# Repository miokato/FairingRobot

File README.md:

#1 This is Robot Car repository.

# I modified some repository.
This is master branch.

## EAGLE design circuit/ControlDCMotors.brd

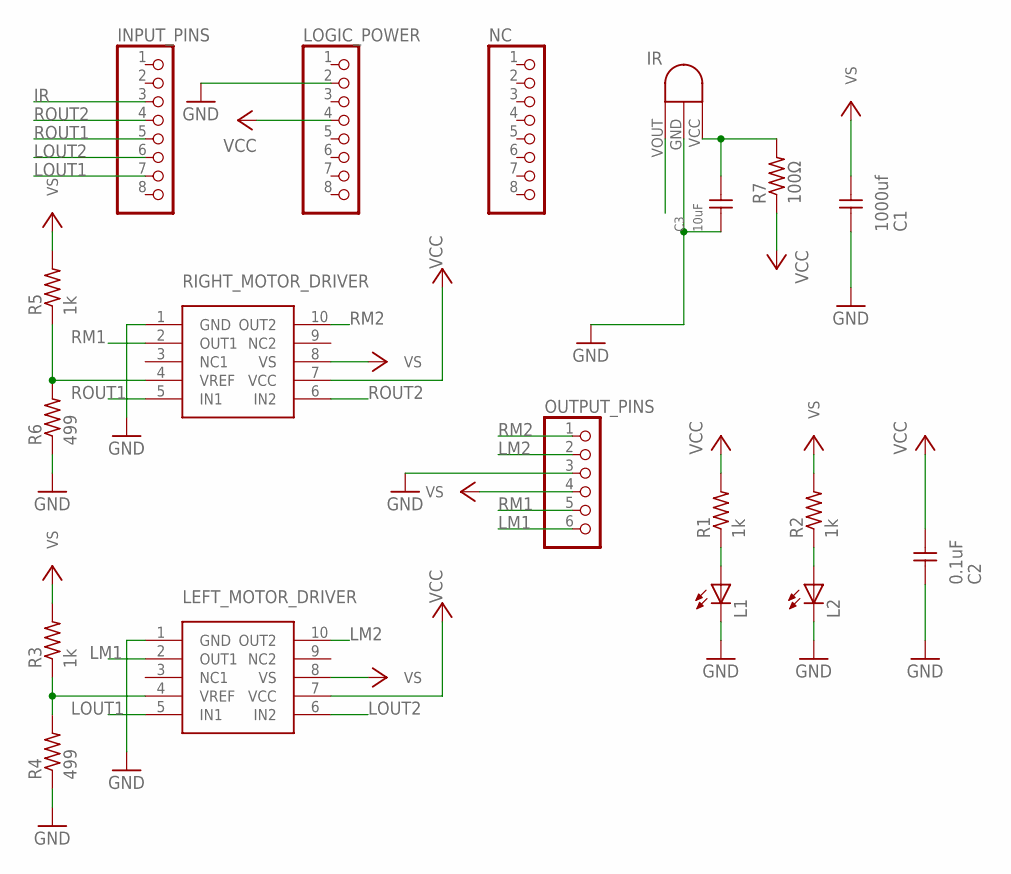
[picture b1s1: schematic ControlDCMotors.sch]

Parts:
C1: 1000uf; EPOL5_10.5
C2: 0.1uF; 1206
C3: 10uF; 1206
INPUT_PINS: PINHD-1X8; 1X08
IR_SENSOR: IR_SENSOR
L1, L2: LED1608
LEFT_MOTOR_DRIVER: TA7291P; HSIP10_P_2.54
LOGIC_POWER: PINHD-1X8; 1X08
NC: PINHD-1X8; 1X08
OUTPUT_PINS: PINHD-1X6; 1X06
R1, R2, R3, R5: 1k; 1206
R4, R6: 499; 1206
R7: 100Ω; 1206
RIGHT_MOTOR_DRIVER: TA7291P; HSIP10_P_2.54

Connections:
GND: C1.-, C2.1, C3.1, IR_SENSOR.GND, L1.C, L2.C, LEFT_MOTOR_DRIVER.1 (GND), LOGIC_POWER.2, OUTPUT_PINS.3, R4.1, R6.1, RIGHT_MOTOR_DRIVER.1 (GND)
IR: INPUT_PINS.3, IR_SENSOR.VOUT
LM1: LEFT_MOTOR_DRIVER.2 (OUT1), OUTPUT_PINS.6
LM2: LEFT_MOTOR_DRIVER.10 (OUT2), OUTPUT_PINS.2
LOUT1: INPUT_PINS.7, LEFT_MOTOR_DRIVER.5 (IN1)
LOUT2: INPUT_PINS.6, LEFT_MOTOR_DRIVER.6 (IN2)
unnamed: L1.A, R1.1
unnamed: L2.A, R2.1
unnamed: R5.1, R6.2, RIGHT_MOTOR_DRIVER.4 (VREF)
unnamed: LEFT_MOTOR_DRIVER.4 (VREF), R3.1, R4.2
unnamed: C3.2, IR_SENSOR.VCC, R7.2
RM1: OUTPUT_PINS.5, RIGHT_MOTOR_DRIVER.2 (OUT1)
RM2: OUTPUT_PINS.1, RIGHT_MOTOR_DRIVER.10 (OUT2)
ROUT1: INPUT_PINS.5, RIGHT_MOTOR_DRIVER.5 (IN1)
ROUT2: INPUT_PINS.4, RIGHT_MOTOR_DRIVER.6 (IN2)
VCC: C2.2, LEFT_MOTOR_DRIVER.7 (VCC), LOGIC_POWER.4, R1.2, R7.1, RIGHT_MOTOR_DRIVER.7 (VCC)
VS: C1.+, LEFT_MOTOR_DRIVER.8 (VS), OUTPUT_PINS.4, R2.2, R3.2, R5.2, RIGHT_MOTOR_DRIVER.8 (VS)

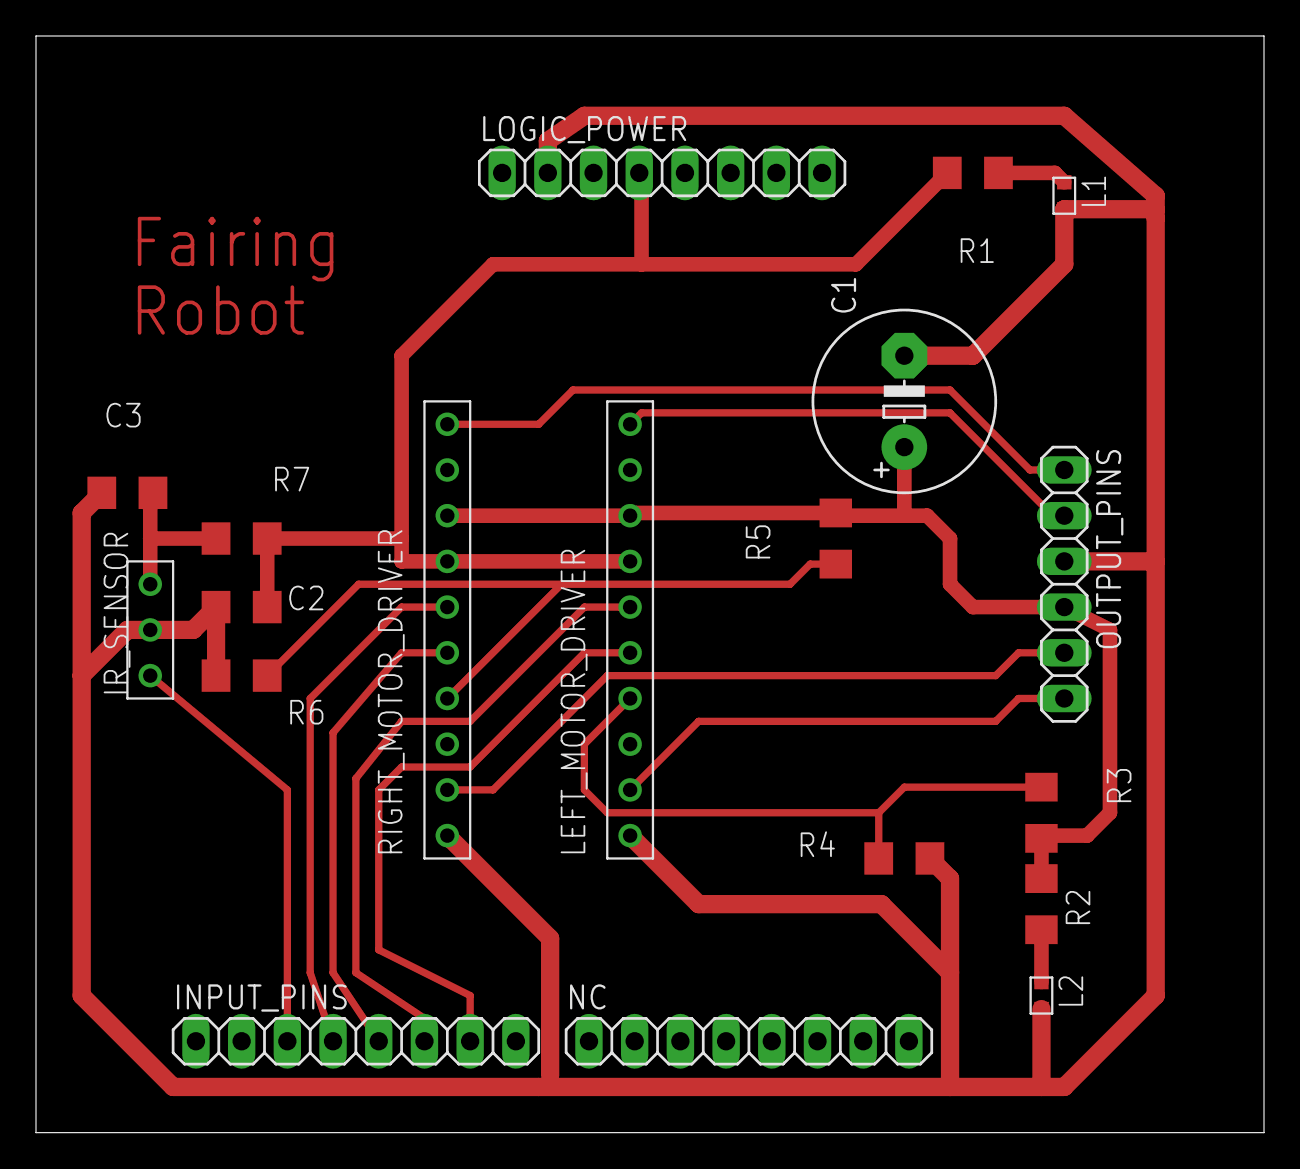
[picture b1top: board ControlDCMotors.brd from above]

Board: 2 copper layers, 68.2 x 61.0 mm, 19 parts (0 on the bottom side), 17 nets.

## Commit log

2015-04-25 add ios program that control robot car
2015-06-14 change place some dir
2015-06-28 add README
2015-07-05 Separate init method of FairingRobot.h file
2015-07-05 test commit
2015-07-05 new develop repo
2015-07-05 modify README.md
2015-07-14 make IrRobot
2015-07-14 modify RobotController.h
2015-07-14 change name
